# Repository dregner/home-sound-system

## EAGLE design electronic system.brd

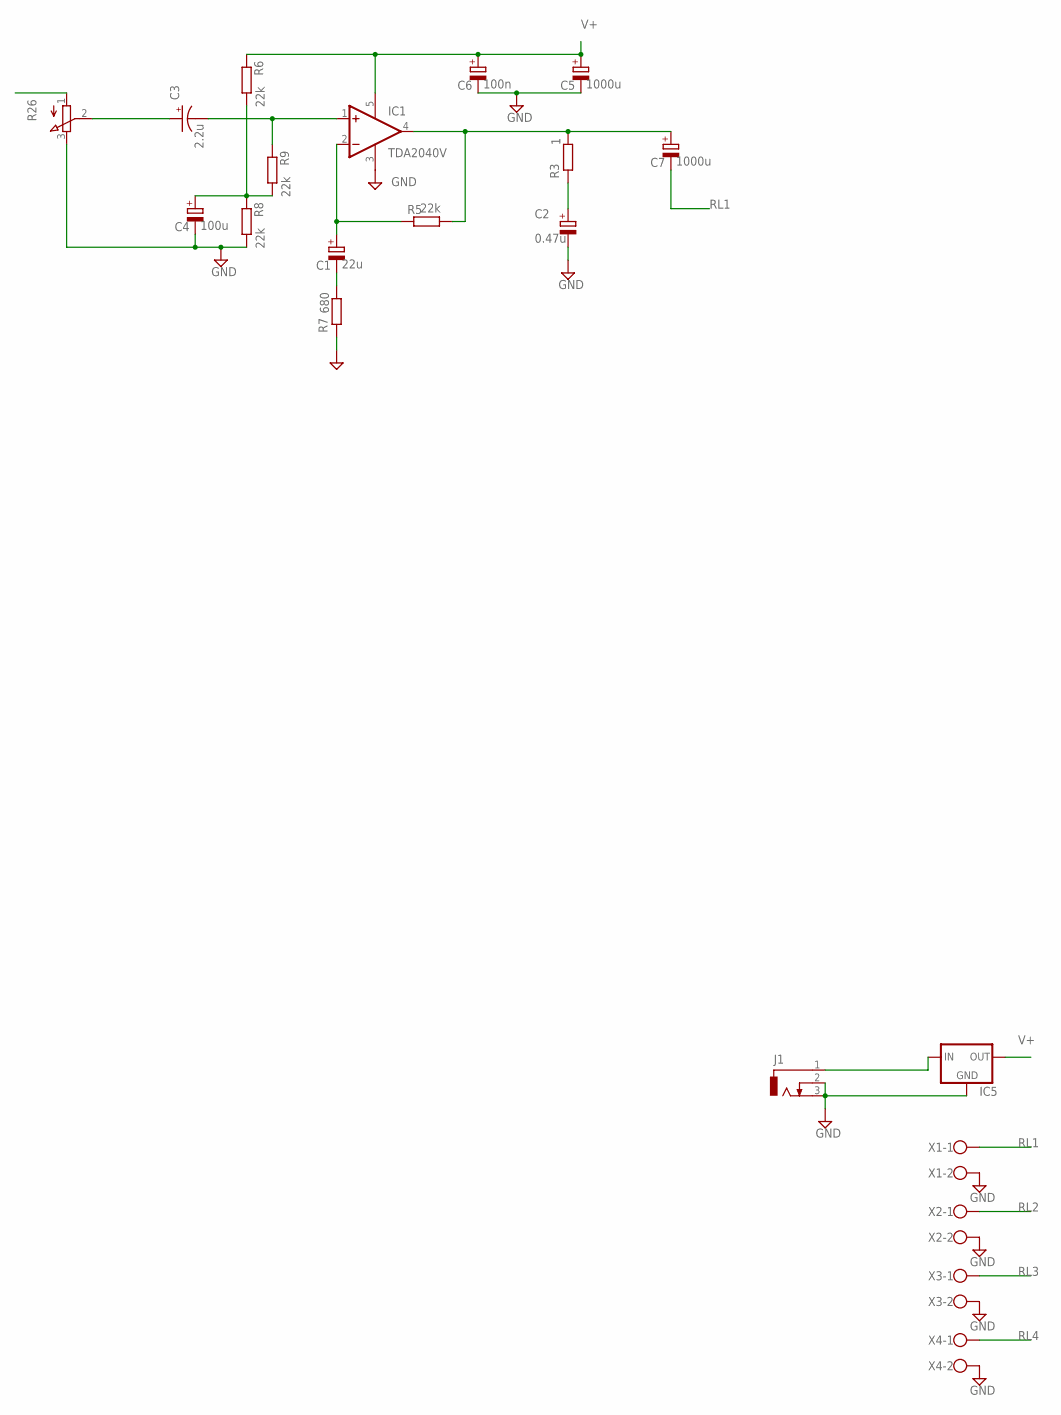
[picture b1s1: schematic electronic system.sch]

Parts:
C1: 22u; E5-6
C2: 0.47u; E5-5
C3: 2.2u; TT5D11
C4: 100u; E5-10,5
C5, C7: 1000u; E5-10,5
C6: 100n; E5-5
IC1: TDA2040V; CB360
IC5: 78XXS
J1: DCJ0303
R3: 1; 0207/12
R5, R6, R8, R9: 22k; 0207/12
R7: 680; 0207/12
R26: 3RP/1610N
X1, X2, X3, X4: W237-102

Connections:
GND: C2.-, C4.-, C5.-, C6.-, IC1.3 (V-), IC5.GND, J1.2, J1.3, R7.2, R8.2, R26.3 (E), X1.2, X2.2, X3.2, X4.2
unnamed: C7.+, IC1.4 (OUT), R3.1, R5.2
unnamed: C2.+, R3.2
unnamed: C1.+, IC1.2 (-IN), R5.1
unnamed: C1.-, R7.1
unnamed: C3.-, IC1.1 (+IN), R9.1
unnamed: C4.+, R6.2, R8.1, R9.2
unnamed: IC5.IN, J1.1
unnamed: C3.+, R26.2 (S)
RL1: C7.-, X1.1
RL2: X2.1
RL3: X3.1
RL4: X4.1
V+: C5.+, C6.+, IC1.5 (V+), IC5.OUT, R6.1

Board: 2 copper layers, 21 parts (0 on the bottom side), 11 nets, no tracks yet.

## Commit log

2019-05-01 First Schematic
    Schematic for 1 input and 4 output
2019-05-09 First schematic
    Developing
2019-09-04 V1.0
    Beggining
2019-09-04 Removing
    Wrong version
